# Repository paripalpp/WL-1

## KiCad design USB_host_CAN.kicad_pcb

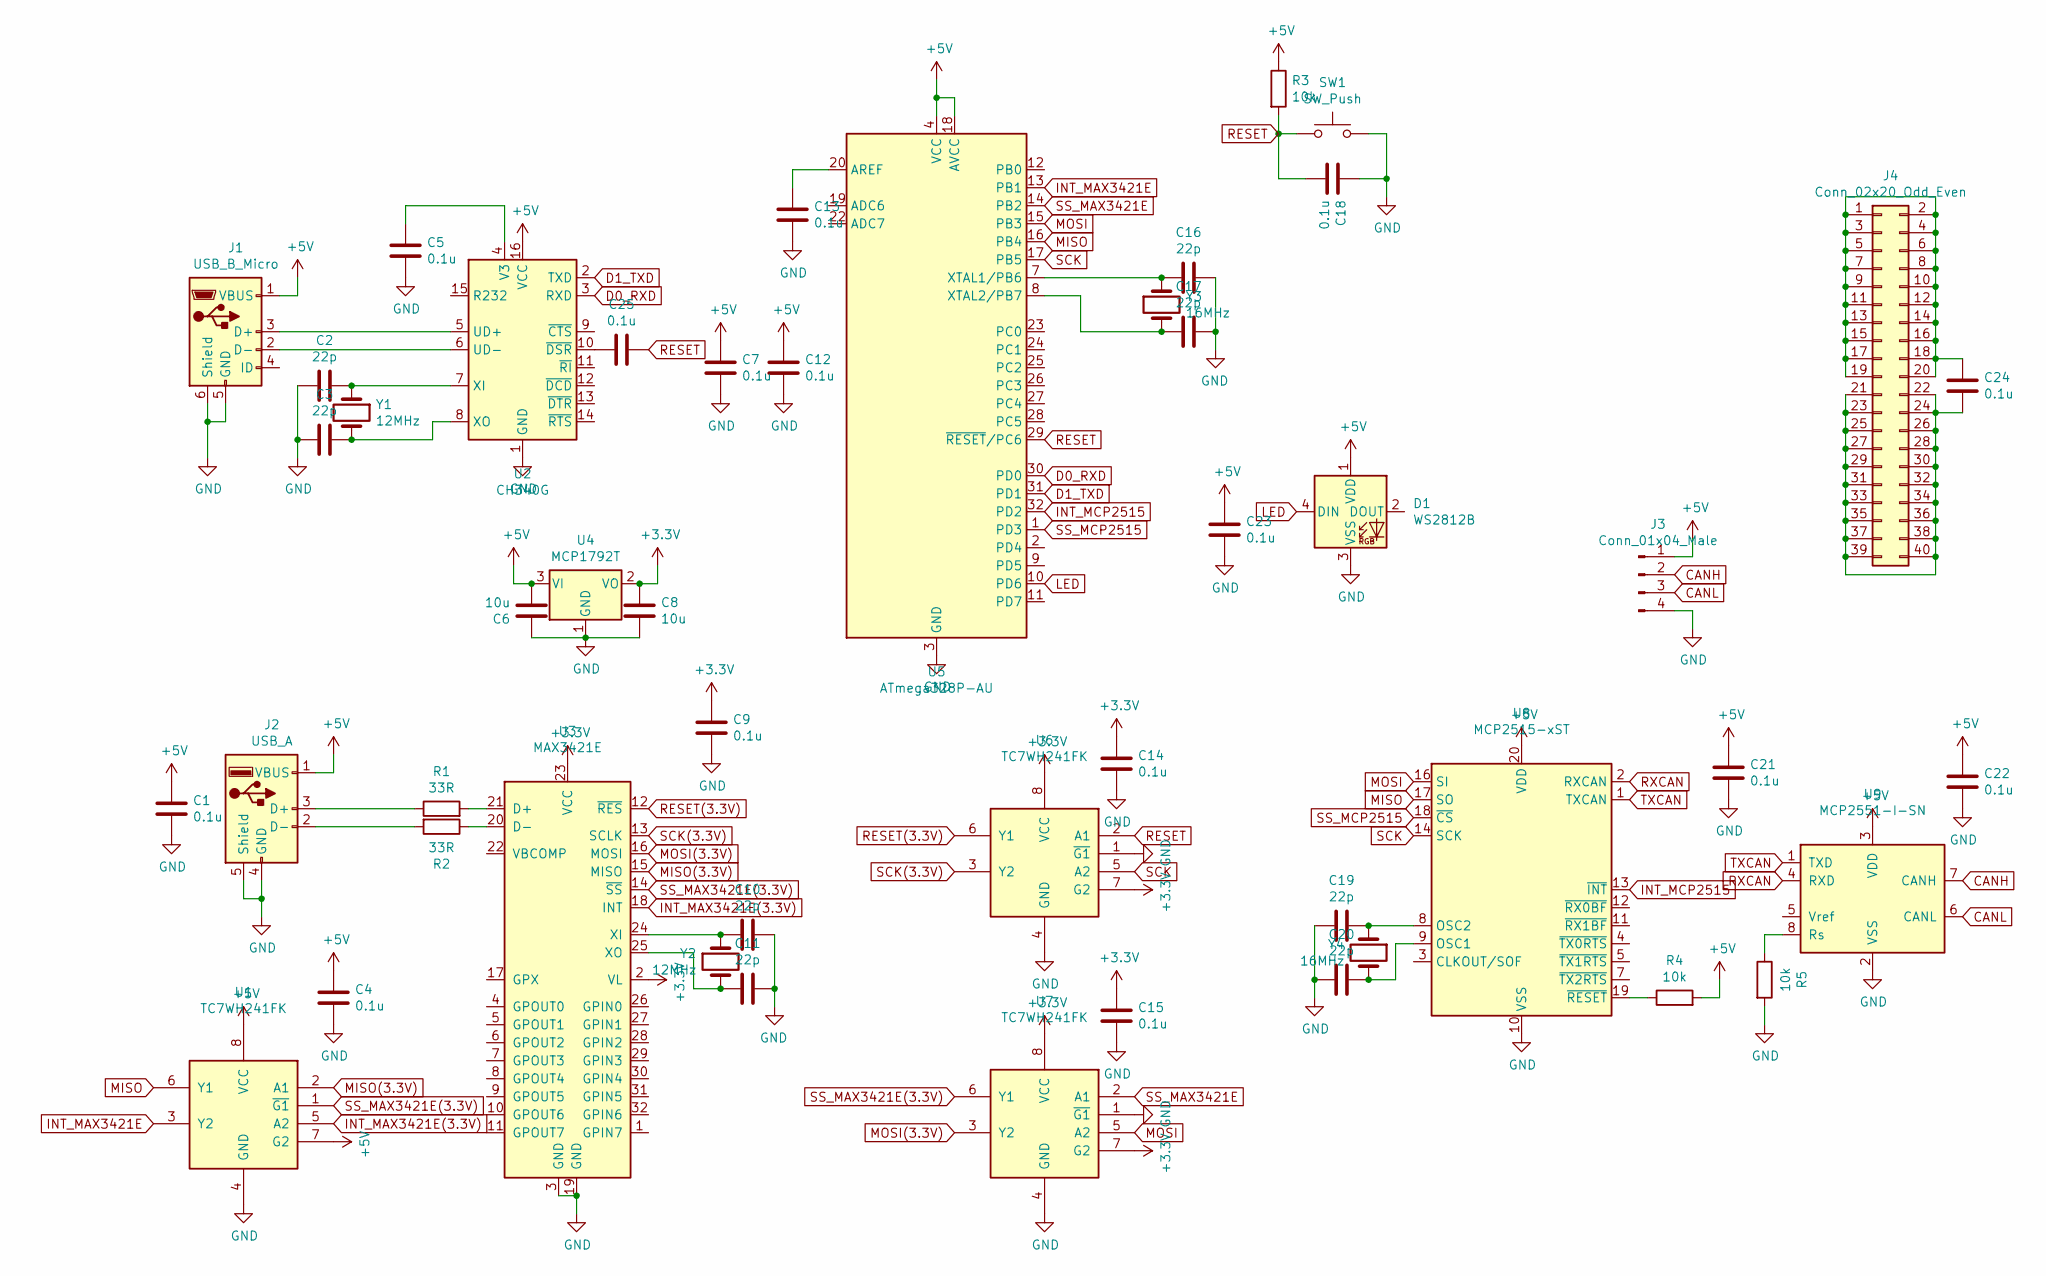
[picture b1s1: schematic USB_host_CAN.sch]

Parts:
C1, C4, C5, C7, C9, C12, C13, C14, C15, C18, C21, C22, C23, C24, C25: 0.1u; C_0603_1608Metric
C2, C3, C10, C11, C16, C17, C19, C20: 22p; C_0603_1608Metric
C6, C8: 10u; C_0805_2012Metric
D1: WS2812B; LED_WS2812B_PLCC4_5.0x5.0mm_P3.2mm
J1: USB_B_Micro; USB_Micro-B_Molex_47346-0001
J2: USB_A; USB_A_Stewart_SS-52100-001_Horizontal
J3: Conn_01x04_Male; PinHeader_1x04_P2.54mm_Horizontal_Mirror
J4: Conn_02x20_Odd_Even; PinHeader_2x20_P2.54mm_Horizontal_Mirror
R1, R2: 33R; R_0603_1608Metric
R3, R4, R5: 10k; R_0603_1608Metric
SW1: SW_Push; switch_smd
U1, U6, U7: TC7WH241FK; VSSOP-8_2.4x2.1mm_P0.5mm
U2: CH340G; SOIC-16_3.9x9.9mm_P1.27mm
U3: MAX3421E; LQFP-32_5x5mm_P0.5mm
U4: MCP1792T; SOT-23
U5: ATmega328P-AU; TQFP-32_7x7mm_P0.8mm
U8: MCP2515-xST; TSSOP-20_4.4x6.5mm_P0.65mm
U9: MCP2551-I-SN; SOIC-8_3.9x4.9mm_P1.27mm
Y1, Y2: 12MHz; Crystal_HC50_Vertical
Y3, Y4: 16MHz; Crystal_HC50_Vertical

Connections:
+3V3: C8.1, C9.1, C14.1, C15.1, U3.2 (VL), U3.23 (VCC), U4.2 (VO), U6.7 (G2), U6.8 (VCC), U7.7 (G2), U7.8 (VCC)
+5V: C1.1, C4.1, C6.2, C7.1, C12.1, C21.1, C22.1, C23.1, D1.1 (VDD), J1.1 (VBUS), J2.1 (VBUS), J3.1, R3.1, R4.2, U1.7 (G2), U1.8 (VCC), U2.16 (VCC), U4.3 (VI), U5.4 (VCC), U5.6 (VCC), U5.18 (AVCC), U8.20 (VDD), U9.3 (VDD)
CANH: J3.2, U9.7 (CANH)
CANL: J3.3, U9.6 (CANL)
D0_RXD: U2.3 (RXD), U5.30 (PD0)
D1_TXD: U2.2 (TXD), U5.31 (PD1)
GND: C1.2, C2.1, C3.1, C4.2, C5.2, C6.1, C7.2, C8.2, C9.2, C10.1, C11.1, C12.2, C13.2, C14.2, C15.2, C16.1, C17.1, C18.1, C19.1, C20.1, C21.2, C22.2, C23.2, D1.3 (VSS), J1.5 (GND), J1.6 (Shield), J2.4 (GND), J2.5 (Shield), J3.4, R5.2, SW1.2, U1.4 (GND), U2.1 (GND), U3.3 (GND), U3.19 (GND), U4.1 (GND), U5.3 (GND), U5.5 (GND), U5.21 (GND), U6.1 (~G1~), U6.4 (GND), U7.1 (~G1~), U7.4 (GND), U8.10 (VSS), U9.2 (VSS)
INT_MAX3421E: U1.3 (Y2), U5.13 (PB1)
INT_MAX3421E(3.3V): U1.5 (A2), U3.18 (INT)
INT_MCP2515: U5.32 (PD2), U8.13 (~INT)
LED: D1.4 (DIN), U5.10 (PD6)
MISO: U1.6 (Y1), U5.16 (PB4), U8.17 (SO)
MISO(3.3V): U1.2 (A1), U3.15 (MISO)
MOSI: U5.15 (PB3), U7.5 (A2), U8.16 (SI)
MOSI(3.3V): U3.16 (MOSI), U7.3 (Y2)
unnamed: C2.2, U2.7 (XI), Y1.1
unnamed: C3.2, U2.8 (XO), Y1.2
unnamed: C5.1, U2.4 (V3)
unnamed: C10.2, U3.24 (XI), Y2.1
unnamed: C11.2, U3.25 (XO), Y2.2
unnamed: C13.1, U5.20 (AREF)
unnamed: C16.2, U5.7 (XTAL1/PB6), Y3.1
unnamed: C17.2, U5.8 (XTAL2/PB7), Y3.2
unnamed: C19.2, U8.8 (OSC2), Y4.1
unnamed: C20.2, U8.9 (OSC1), Y4.2
unnamed: C24.1, J4.1, J4.2, J4.3, J4.4, J4.5, J4.6, J4.7, J4.8, J4.9, J4.10, J4.11, J4.12, J4.13, J4.14, J4.15, J4.16, J4.17, J4.18, J4.19, J4.20
unnamed: C24.2, J4.21, J4.22, J4.23, J4.24, J4.25, J4.26, J4.27, J4.28, J4.29, J4.30, J4.31, J4.32, J4.33, J4.34, J4.35, J4.36, J4.37, J4.38, J4.39, J4.40
unnamed: C25.2, U2.10 (~DSR)
unnamed: J1.2 (D-), U2.6 (UD-)
unnamed: J1.3 (D+), U2.5 (UD+)
unnamed: J2.2 (D-), R2.2
unnamed: J2.3 (D+), R1.1
unnamed: R1.2, U3.21 (D+)
unnamed: R2.1, U3.20 (D-)
unnamed: R4.1, U8.19 (~RESET)
unnamed: R5.1, U9.8 (Rs)
RESET: C18.2, C25.1, R3.2, SW1.1, U5.29 (~RESET~/PC6), U6.2 (A1)
RESET(3.3V): U3.12 (~RES~), U6.6 (Y1)
RXCAN: U8.2 (RXCAN), U9.4 (RXD)
SCK: U5.17 (PB5), U6.5 (A2), U8.14 (SCK)
SCK(3.3V): U3.13 (SCLK), U6.3 (Y2)
SS_MAX3421E: U5.14 (PB2), U7.2 (A1)
SS_MAX3421E(3.3V): U1.1 (~G1~), U3.14 (~SS~), U7.6 (Y1)
SS_MCP2515: U5.1 (PD3), U8.18 (~CS)
TXCAN: U8.1 (TXCAN), U9.1 (TXD)

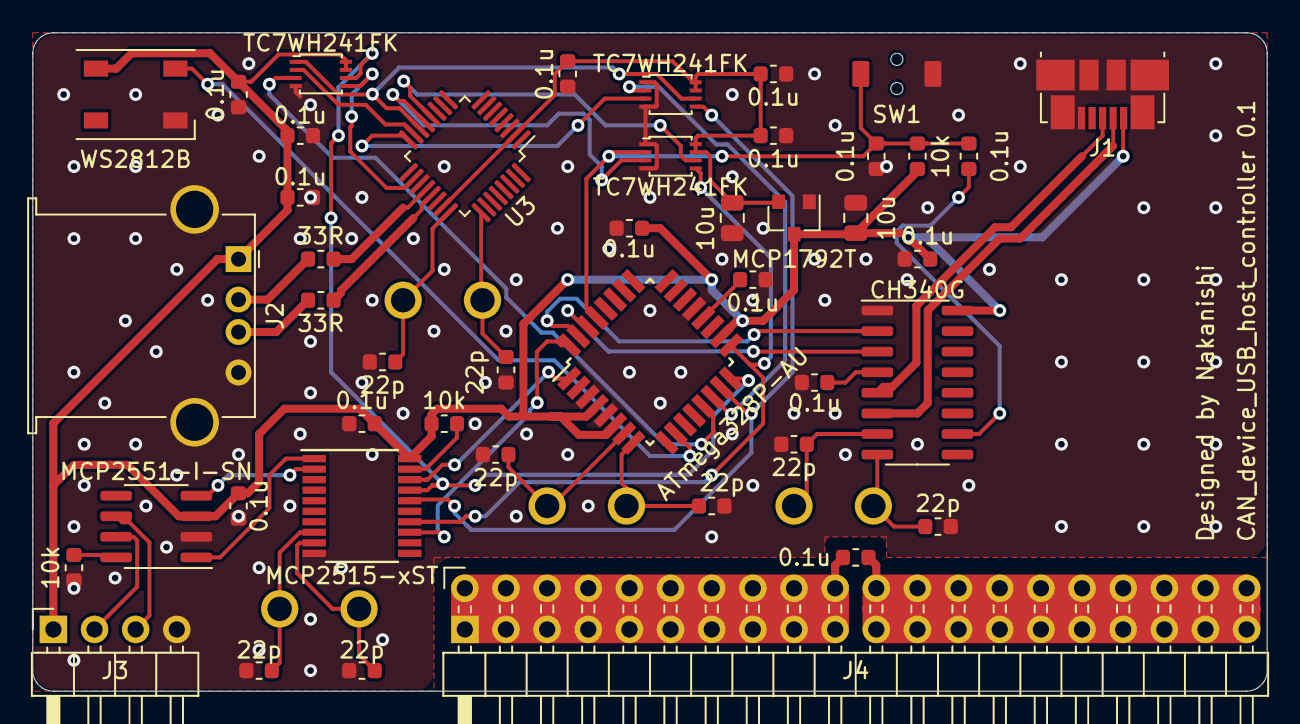
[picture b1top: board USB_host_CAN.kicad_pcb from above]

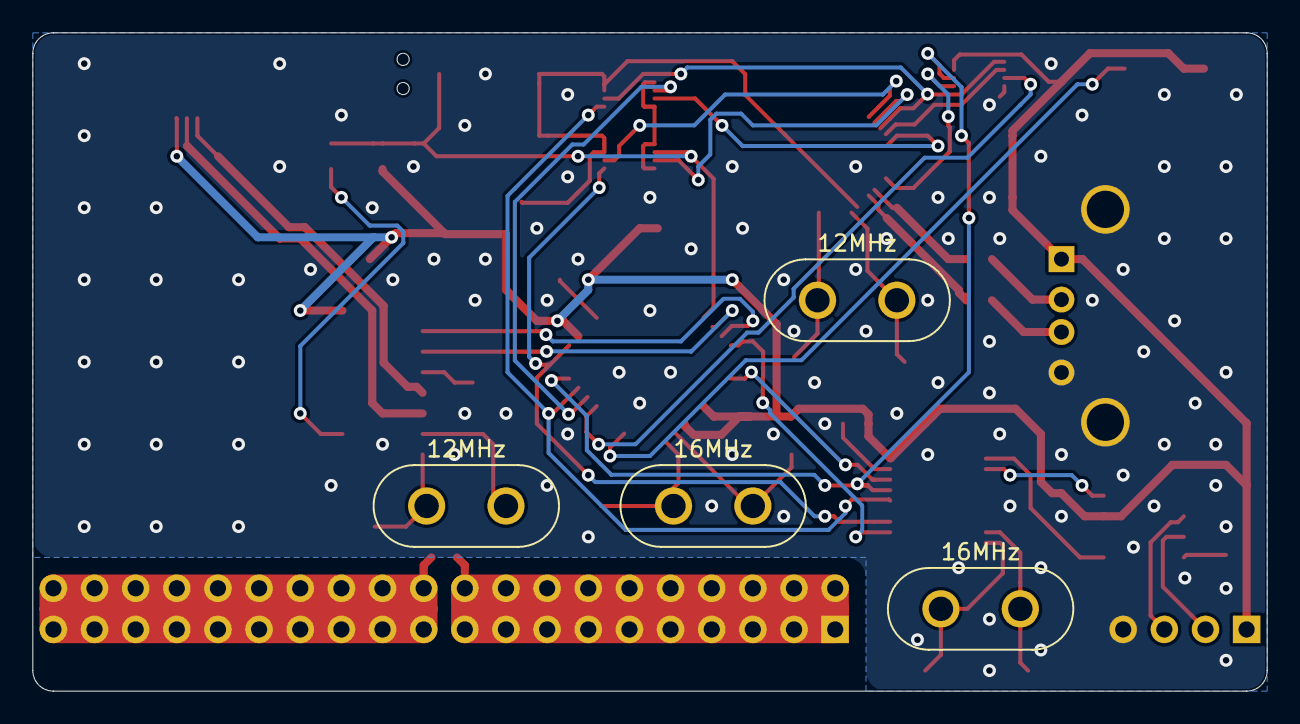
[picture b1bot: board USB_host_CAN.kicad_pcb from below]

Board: 2 copper layers, 76.2 x 40.6 mm, 49 parts (4 on the bottom side), 45 nets.
